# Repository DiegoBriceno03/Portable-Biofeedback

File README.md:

# Portable Biofeedback Device Repository

A repository that stores hardware and software files developed for the Portable Biofeedback Device, as worked on and built by students in the Electrical & Computer Engineering (ECE) Department of the College of Engineering & Computer Science (CECS) at the University of Central Florida (UCF) in Orlando, Florida.

The accompanying Android app was developed in Android Studio 3.5.3, making use of Android SDK/API 21 (Android 5).

All the schematics and layout is done in Kicad 5.14 along with custom libraries. These libraries are added under /Libraries.

These projects use custom path for its libraries. The custom Kicad Path variable ${KI_SDREPO} is used to increase portability. Custom variable points to the physical location of the /Libraries directory and must be declared under "Preferences > Configure Paths" setting before use.

## Group 11 Members

Roles are listed under each group member

+ Grace Brazil (EE)
  + Power circuit design
+ Diego Briceno (EE)
  + PCB design
+ Gustavo Diaz Galeas (CpE)
  + Phone app development
+ Nicholas Miller (CpE)
  + Firmware development

## Hardware

### Breakout Boards
- [x] MAX30101 Heart Rate / Pulse Oximeter Breakout Board REV -
- [x] Galvanic Skin Response Sensor (Groove Seed GSR Sensor design used: https://www.seeedstudio.com/Grove-GSR-sensor-p-1614.html.html)
- [x] Temperature Sensor Supporting Hardware
- [x] Battery Charging Managing circuit (BMS)
- [x] Power Regulation
Integration of these hardware is seen under ~/Prototyp_REV- 

## Software
### Phone App
- [x] Bluetooth backend
- [X] UI / UX

### Firmware
- [x] Heart Rate Data Processing Algorithm
- [x] Temperature Data Processing Algorithm
- [x] Galvanic Skin Resistance Data Processing Algorithm

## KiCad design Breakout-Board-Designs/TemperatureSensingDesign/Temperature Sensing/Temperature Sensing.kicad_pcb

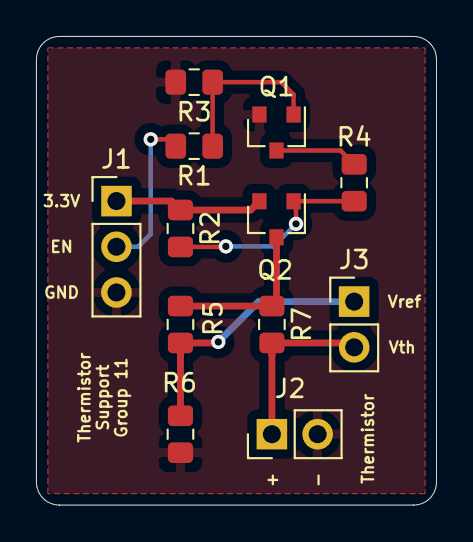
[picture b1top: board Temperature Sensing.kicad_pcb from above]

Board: 2 copper layers, 22.2 x 26.0 mm, 12 parts (0 on the bottom side), 9 nets.

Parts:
J1: POW / Control; PinHeader_1x03_P2.54mm_Vertical
J2: Termistor 10k; PinHeader_1x02_P2.54mm_Vertical
J3: ADC Inputs; PinHeader_1x02_P2.54mm_Vertical
Q1: 2N7002E; SOT-23
Q2: BSS83P; SOT-23
R1, R2, R3, R4, R6: 10k; R_0805_2012Metric_Pad1.15x1.40mm_HandSolder
R5, R7: 20k; R_0805_2012Metric_Pad1.15x1.40mm_HandSolder

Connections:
/+3.3V: J1.1, Q2.2, R2.1
/GPIO_EN: J1.2, R1.2
/Vref: J3.1, R5.2, R6.1
/Vth: J2.1, J3.2, R7.2
GND: J1.3, J2.2, Q1.2, R3.2, R6.2
unnamed: Q1.1, R1.1, R3.1
unnamed: Q1.3, R4.2
unnamed: Q2.1, R2.2, R4.1
unnamed: Q2.3, R5.1, R7.1

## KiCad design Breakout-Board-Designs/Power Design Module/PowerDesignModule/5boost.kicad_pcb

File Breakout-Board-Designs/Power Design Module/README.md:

# Power Design Module.

This module contains the design for the Portable biofeedback anxiety treatment device. 
It consist of a charging circuit (BQ24072) which is configured to charge a single cell LiPo(PKCELL 503035) 500mAh battery. This design takes advantage of a Micro USB charging at CV of 4.2V and CC of 500mA.

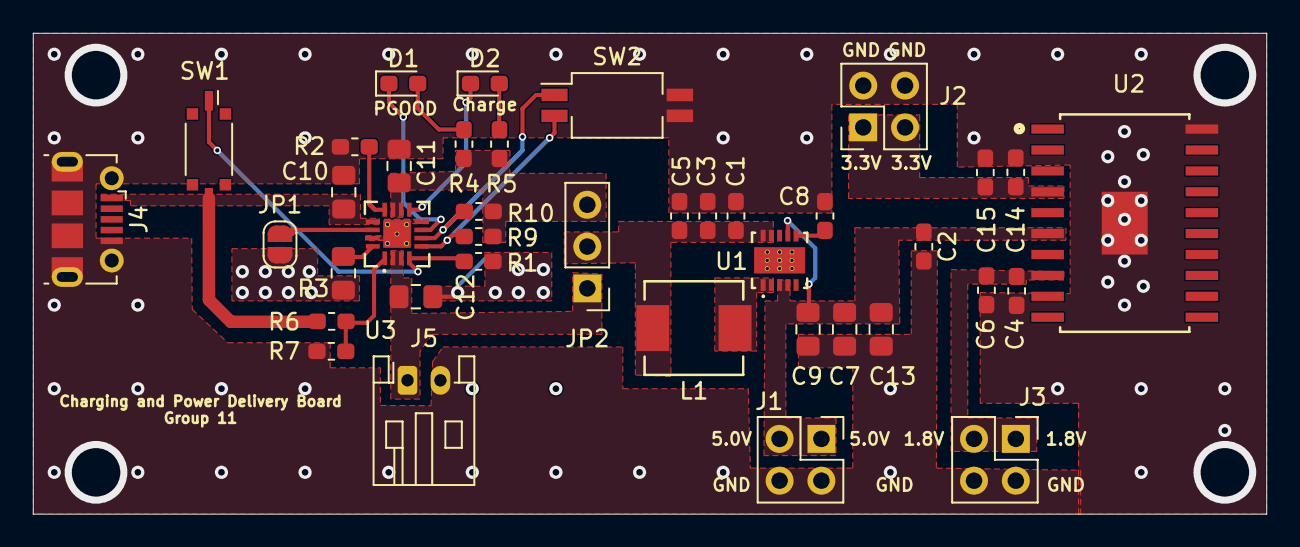
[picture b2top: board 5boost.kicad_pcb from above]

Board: 2 copper layers, 74.9 x 29.2 mm, 39 parts (0 on the bottom side), 21 nets.

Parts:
C1, C3, C5: 10μF; C_0603_1608Metric_Pad1.05x0.95mm_HandSolder
C2, C4, C14: 0.1uF; C_0603_1608Metric_Pad1.05x0.95mm_HandSolder
C6, C15: 10uF; C_0603_1608Metric_Pad1.05x0.95mm_HandSolder
C7, C9, C13: 10uF; C_0805_2012Metric_Pad1.15x1.40mm_HandSolder
C8: 22nF; C_0603_1608Metric_Pad1.05x0.95mm_HandSolder
C10: 1uF; C_0805_2012Metric_Pad1.15x1.40mm_HandSolder
C11, C12: 4.7uF; C_0805_2012Metric_Pad1.15x1.40mm_HandSolder
D1: Red; LED_0603_1608Metric_Pad1.05x0.95mm_HandSolder
D2: Green; LED_0603_1608Metric_Pad1.05x0.95mm_HandSolder
J1: 5.0V; PinSocket_2x02_P2.54mm_Vertical
J2: 3.3V; PinSocket_2x02_P2.54mm_Vertical
J3: 1.8V; PinSocket_2x02_P2.54mm_Vertical
J4: USB_B_Micro; USB_Micro-B_Molex-105017-0001
J5: Battery Output; JST_PH_S2B-PH-K_1x02_P2.00mm_Horizontal
JP1: TMR OFF; SolderJumper-2_P1.3mm_Open_RoundedPad1.0x1.5mm
JP2: Charger / Battery Bypass; PinHeader_1x03_P2.54mm_Vertical
L1: 1uH; IHLP2020BZER1R0M01
R1, R2: 2K; R_0603_1608Metric_Pad1.05x0.95mm_HandSolder
R3: 1.78k; R_0805_2012Metric_Pad1.15x1.40mm_HandSolder
R4: 530R; R_0603_1608Metric_Pad1.05x0.95mm_HandSolder
R5: 320R; R_0603_1608Metric_Pad1.05x0.95mm_HandSolder
R6: 200k; R_0603_1608Metric_Pad1.05x0.95mm_HandSolder
R7: 49.9k; R_0603_1608Metric_Pad1.05x0.95mm_HandSolder
R9, R10: 10k; R_0603_1608Metric_Pad1.05x0.95mm_HandSolder
SW1: Charge Disable Switch; SW_DIP_SPSTx01_Slide_Copal_CVS-01xB_W5.9mm_P1mm
SW2: Input Current Selection; SW_DIP_SPSTx02_Slide_Copal_CHS-02B_W7.62mm_P1.27mm
U1: DRC_S-PVSON-N10; TPS61232DRCR
U2: TPPM0110DWPR
U3: BQ24072TRGTR

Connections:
/1.8V: C4.1, C6.1, J3.1, J3.2, U2.8
/3.3V: C14.1, C15.1, J2.1, J2.2, U2.4
/5.0V: C2.1, C7.1, C9.1, C13.1, J1.1, J1.2, U1.3, U1.4, U1.7, U2.6
/ChargingCircuit/BATT+: C12.1, J5.1, JP2.1, U3.2, U3.3
/Voutbat: C1.2, C3.2, C5.2, JP2.2, L1.1, U1.9, U1.10
EN1: R10.2, SW2.1, U3.6
EN2: R9.1, SW2.2, U3.5
GND: C1.1, C2.2, C3.1, C4.2, C5.1, C6.2, C7.2, C8.2, C9.2, C10.2, C11.2, C12.2, C13.2, C14.2, C15.2, J1.3, J1.4, J2.3, J2.4, J3.3, J3.4, J4.5, J4.6, J5.2, JP1.2, R1.2, R2.2, R3.2, R7.2, SW2.3, SW2.4, U1.11, U2.20, U2.21, U3.8, U3.15, U3.17
unnamed: C8.1, U1.6
unnamed: D1.1, U3.7
unnamed: D1.2, R4.2
unnamed: D2.1, U3.9
unnamed: D2.2, R5.2
unnamed: JP1.1, U3.14
unnamed: L1.2, U1.1, U1.2
unnamed: R2.1, U3.12
unnamed: R3.1, U3.16
unnamed: R6.2, R7.1, U3.1
Vbus: C10.1, J4.1, R6.1, SW1.2, U3.13
Vout: C11.1, JP2.3, R4.1, R5.1, R9.2, R10.1, U3.10, U3.11
~CE: R1.1, SW1.1, U3.4

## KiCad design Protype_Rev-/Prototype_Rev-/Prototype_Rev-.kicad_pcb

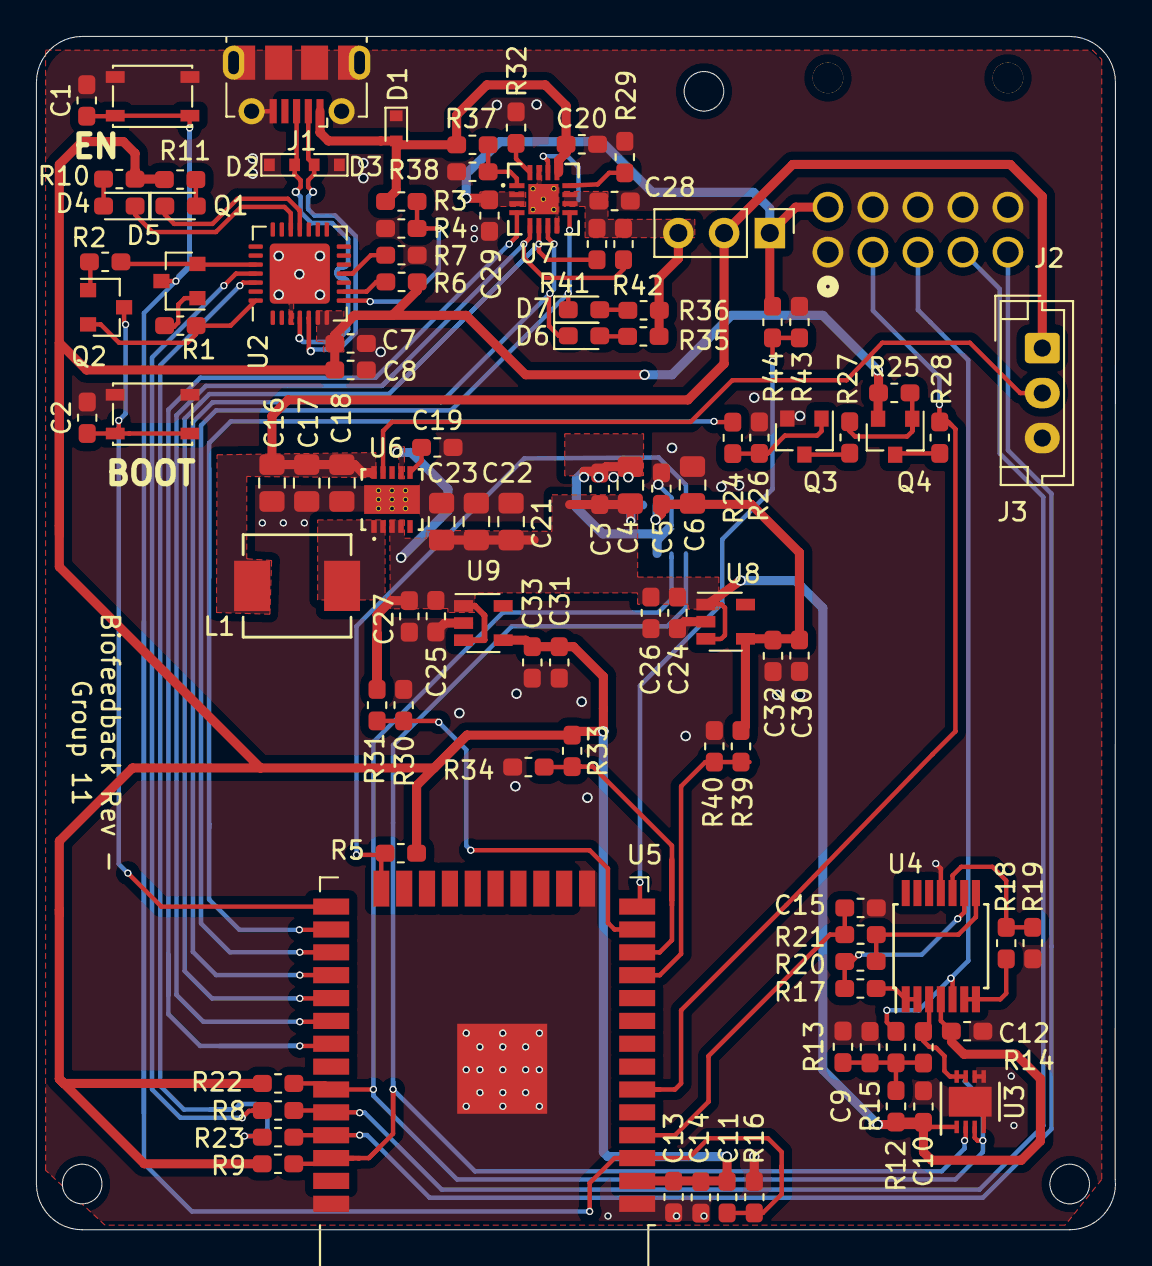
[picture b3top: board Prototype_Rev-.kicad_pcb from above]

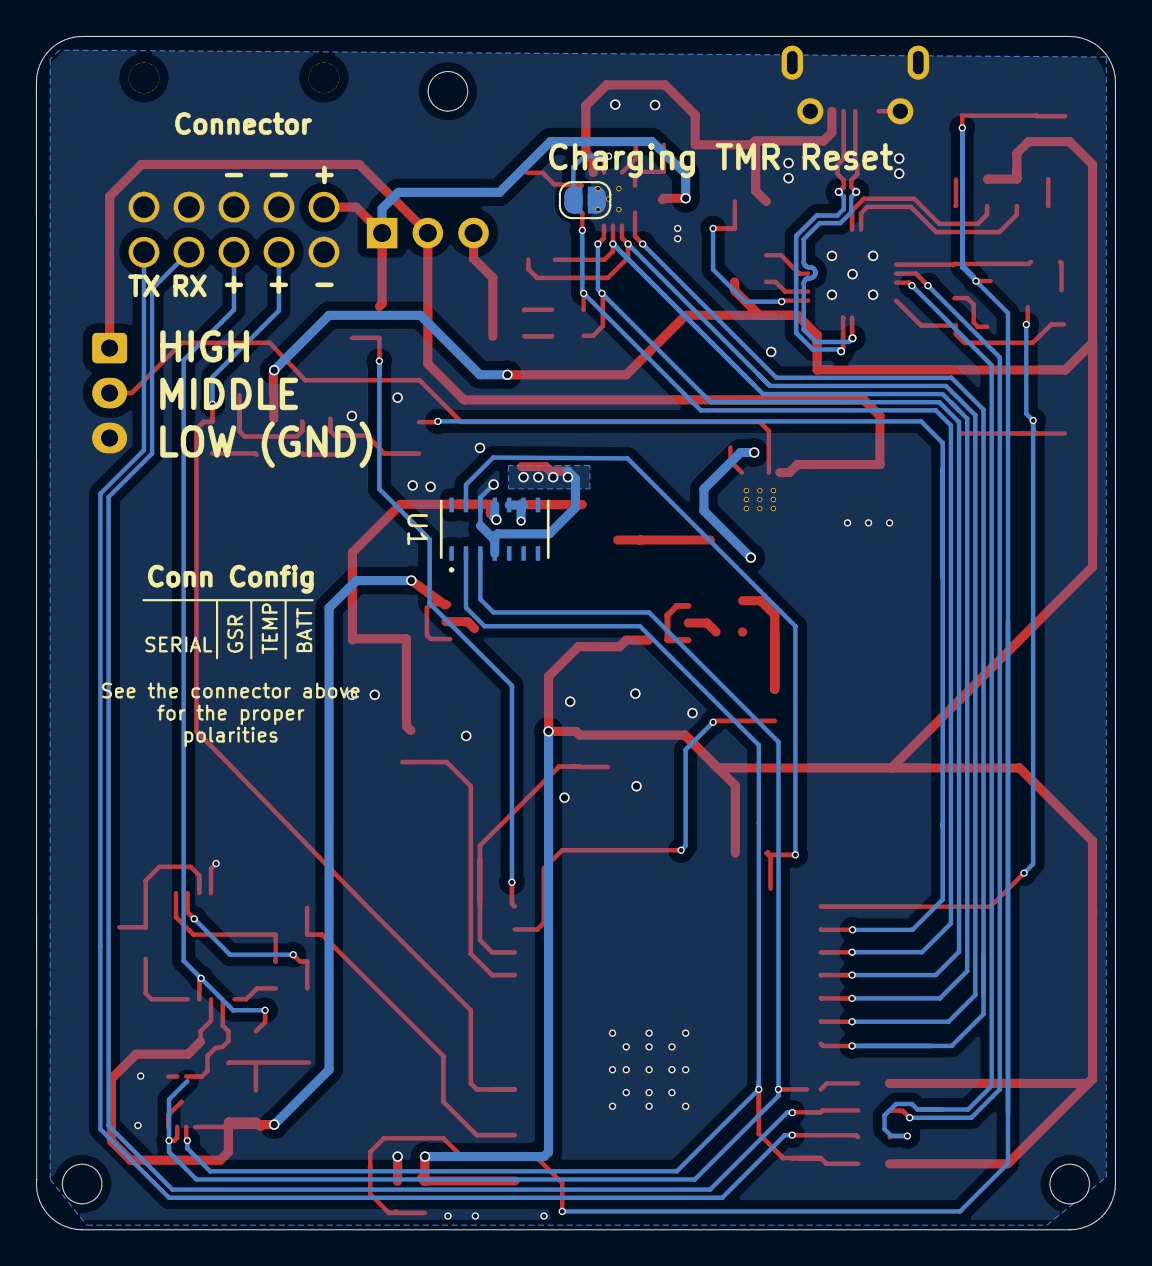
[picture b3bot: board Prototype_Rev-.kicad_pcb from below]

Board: 2 copper layers, 59.9 x 66.3 mm, 106 parts (3 on the bottom side), 64 nets.

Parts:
C1, C2, C7, C10, C11, C12, C13: 0.1uF; C_0603_1608Metric_Pad1.05x0.95mm_HandSolder
C3, C5, C20, C24, C25, C26, C27, C30, C31, C32, C33: 1uF; C_0603_1608Metric_Pad1.05x0.95mm_HandSolder
C4, C6, C16, C17, C18, C21, C22, C23: 10uF; C_0805_2012Metric_Pad1.15x1.40mm_HandSolder
C8, C9, C28, C29: 4.7uF; C_0603_1608Metric_Pad1.05x0.95mm_HandSolder
C14: 22uF; C_0603_1608Metric_Pad1.05x0.95mm_HandSolder
C15: 100nF; C_0603_1608Metric_Pad1.05x0.95mm_HandSolder
C19: 22nF; C_0603_1608Metric_Pad1.05x0.95mm_HandSolder
D1, D2, D3: DESD5V0S1BB-7; D_SOD-523
D4, D5, D6: Red; LED_0603_1608Metric_Pad1.05x0.95mm_HandSolder
D7: Green; LED_0603_1608Metric_Pad1.05x0.95mm_HandSolder
J1: USB_B_Micro; USB_Micro-B_Molex-105017-0001
J2: Interface Hub; 1053141110
J3: Conn_01x02; JST_EH_B3B-EH-A_1x03_P2.50mm_Vertical
JP1: TMR OFF; SolderJumper-2_P1.3mm_Open_RoundedPad1.0x1.5mm
JP2: Charger / Battery Bypass; PinHeader_1x03_P2.54mm_Vertical
L1: 1uH; IHLP2020BZER1R0M01
NT1: AGND - GND; NetTie-2_SMD_Pad0.5mm
Q1, Q2: SS8050-G; SOT-23
Q3: 2N7002ET7G; SOT-23
Q4: BSS83P; SOT-23
R1, R2, R7, R16, R24, R25, R26, R27, R28, R41, R42: 10k; R_0603_1608Metric_Pad1.05x0.95mm_HandSolder
R3: 22.1k; R_0603_1608Metric_Pad1.05x0.95mm_HandSolder
R4: 47.5k; R_0603_1608Metric_Pad1.05x0.95mm_HandSolder
R5, R22, R23: 1.5k; R_0603_1608Metric_Pad1.05x0.95mm_HandSolder
R6, R29: 2K; R_0603_1608Metric_Pad1.05x0.95mm_HandSolder
R8, R9: 0R; R_0603_1608Metric_Pad1.05x0.95mm_HandSolder
R10, R11, R35: 530R; R_0603_1608Metric_Pad1.05x0.95mm_HandSolder
R12, R13: 4.7k; R_0603_1608Metric_Pad1.05x0.95mm_HandSolder
R14, R15, R19, R20, R37: 200k; R_0603_1608Metric_Pad1.05x0.95mm_HandSolder
R17, R18, R30, R31, R33, R34, R39, R40, R43, R44: 100k; R_0603_1608Metric_Pad1.05x0.95mm_HandSolder
R21: 1M; R_0603_1608Metric_Pad1.05x0.95mm_HandSolder
R32: 1.78k; R_0603_1608Metric_Pad1.05x0.95mm_HandSolder
R36: 320R; R_0603_1608Metric_Pad1.05x0.95mm_HandSolder
R38: 49.9k; R_0603_1608Metric_Pad1.05x0.95mm_HandSolder
SW1: EN; SW_SPST_PTS810
SW2: BOOT; SW_SPST_PTS810
U1: MAX30101EFD+
U2: CP2102N-A01-GQFN28; QFN-28-1EP_5x5mm_P0.5mm_EP3.35x3.35mm
U3: MAX5419LETA+; DFN-8-1EP_3x3mm_P0.5mm_EP1.66x2.38mm
U4: LM324; TSSOP-14_4.4x5mm_P0.65mm
U5: ESP32-WROOM-32
U6: TPS61232DRCR
U7: BQ24072TRGTR
U8: TLV75718PDBVR; SOT-23-5
U9: TLV75733PDBVR; SOT-23-5

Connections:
+1V8: C5.1, C6.1, C30.1, C32.1, R39.1, U1.11, U8.4
+3V3: C7.1, C8.1, C13.1, C14.1, C31.1, C33.1, Q4.2, R5.1, R6.1, R10.1, R11.1, R16.1, R22.1, R23.1, R25.1, R33.1, U2.6, U2.7, U5.2, U9.4
+5V: C3.1, C4.1, C10.1, C12.1, C21.1, C22.1, C23.1, C24.1, C25.1, C26.1, C27.1, R12.1, R30.1, U1.9, U1.10, U3.1, U4.4, U6.3, U6.4, U6.7, U8.1, U8.3, U9.1, U9.3
/1.8V_MON: R39.2, R40.1, U5.11
/3.3V_MON: R33.2, R34.1, U5.12
/5V_MON: R30.2, R31.1, U5.13
/BATT+: C29.1, J2.6, JP2.1, R43.1, U7.2, U7.3
/BATT+_MON: R43.2, R44.1, U5.14
/CHRG_EN1: R42.2, U5.29, U7.6
/CHRG_EN2: R41.1, U5.30, U7.5
/EN: C1.1, C11.1, Q1.3, R16.2, SW1.1, U5.3
/GSR+: J2.3, R15.2, U4.5
/GSR_MON: C15.1, R21.2, U5.4
/IO0: C2.1, Q2.3, SW2.1, U5.25
/ON_OFF: J3.2, U6.9
/RXD: R8.1, U2.25
/RXD0: J2.4, R8.2, U5.34
/SCL: R23.2, U1.2, U3.2, U5.36
/SDA: R22.2, U1.3, U3.3, U5.33
/TEMP_EN: R24.2, U5.26
/TXD: R9.2, U2.26
/TXD0: J2.5, R9.1, U5.35
/USB_N: D3.2, J1.2, U2.5
/USB_P: D2.2, J1.3, U2.4
/VOUTBATT: C16.2, C17.2, C18.2, J3.1, JP2.2, L1.1, U6.10
/VTemp: J2.2, R28.2, U5.6
/Vbus: C20.1, D1.2, J1.1, R3.1, R37.1, U7.13
/~BATT_POWGOOD: D6.1, U5.28, U7.7
/~CE: U5.31, U7.4
/~CHRG: D7.1, U5.27, U7.9
/~DTR: Q2.2, R1.1, U2.28
/~INT: R5.2, U1.13, U5.24
/~RTS: Q1.2, R2.1, U2.24
GND: C1.2, C2.2, C5.2, C6.2, C7.2, C8.2, C9.2, C10.2, C11.2, C12.2, C13.2, C14.2, C15.2, C16.1, C17.1, C18.1, C19.1, C20.2, C21.2, C22.2, C23.2, C24.2, C25.2, C26.2, C27.2, C28.2, C29.2, C30.2, C31.2, C32.2, C33.2, D1.1, D2.1, D3.1, J1.5, J1.6, J2.1, J2.7, J2.8, J2.9, J2.10, J3.3, JP1.2, NT1.2, Q3.2, R4.2, R7.2, R13.2, R19.1, R26.2, R29.2, R31.2, R32.2, R34.2, R38.2, R40.2, R44.2, SW1.2, SW2.2, U1.12, U2.3, U2.29, U3.4, U3.5, U3.6, U3.9, U4.11, U5.1, U5.15, U5.38, U5.39, U6.11, U7.8, U7.15, U7.17, U8.2, U9.2
GNDA: C3.2, C4.2, NT1.1, U1.4
unnamed: C9.1, R12.2, R13.1, R14.1, R15.1
unnamed: C19.2, U6.6
unnamed: D4.1, U2.19
unnamed: D4.2, R10.2
unnamed: D5.1, U2.18
unnamed: D5.2, R11.2
unnamed: D6.2, R35.2
unnamed: D7.2, R36.2
unnamed: JP1.1, U7.14
unnamed: L1.2, U6.1, U6.2
unnamed: Q1.1, R1.2
unnamed: Q2.1, R2.2
unnamed: Q3.1, R24.1, R26.1
unnamed: Q3.3, R27.2
unnamed: Q4.1, R25.2, R27.1
unnamed: Q4.3, R28.1
unnamed: R3.2, R4.1, U2.8
unnamed: R6.2, U2.9
unnamed: R7.1, U2.11
unnamed: R14.2, U3.7, U3.8, U4.3
unnamed: R17.1, U4.1, U4.2
unnamed: R17.2, R20.1, U4.9
unnamed: R18.1, U4.6, U4.7
unnamed: R18.2, R19.2, U4.10
unnamed: R20.2, R21.1, U4.8
unnamed: R29.1, U7.12
unnamed: R32.1, U7.16
unnamed: R37.2, R38.1, U7.1
Vout: C28.1, JP2.3, R35.1, R36.1, R41.2, R42.1, U7.10, U7.11

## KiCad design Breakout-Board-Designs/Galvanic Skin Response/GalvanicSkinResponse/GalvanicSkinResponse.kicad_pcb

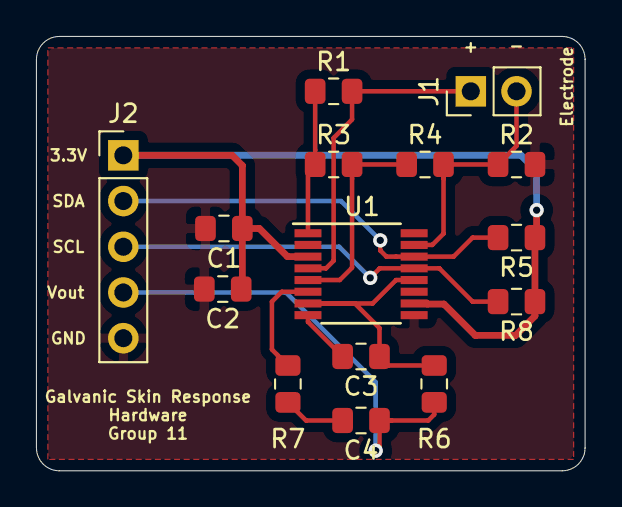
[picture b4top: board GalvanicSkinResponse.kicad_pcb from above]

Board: 2 copper layers, 30.5 x 24.1 mm, 15 parts (0 on the bottom side), 13 nets.

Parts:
C1: 1nF; C_0805_2012Metric_Pad1.15x1.40mm_HandSolder
C2, C4: 10nF; C_0805_2012Metric_Pad1.15x1.40mm_HandSolder
C3: 150pF; C_0805_2012Metric_Pad1.15x1.40mm_HandSolder
J1: Electrodes; PinHeader_1x02_P2.54mm_Vertical
J2: Control; PinHeader_1x05_P2.54mm_Vertical
R1, R6, R7: 100R; R_0805_2012Metric_Pad1.15x1.40mm_HandSolder
R2: 50R; R_0805_2012Metric_Pad1.15x1.40mm_HandSolder
R3: 100k; R_0805_2012Metric_Pad1.15x1.40mm_HandSolder
R4, R5, R8: 15k; R_0805_2012Metric_Pad1.15x1.40mm_HandSolder
U1: PGA309; TSSOP-16_4.4x5mm_P0.65mm

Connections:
+3V3: C1.1, C2.1, J2.1, R5.1, R8.1, U1.3, U1.10
GND: C1.2, C2.2, J2.5, R2.2, U1.2, U1.9, U1.11
unnamed: C3.1, R6.2, U1.7, U1.12
unnamed: C3.2, U1.8
unnamed: C4.2, R7.1
unnamed: J1.1, R1.2, U1.4
unnamed: J1.2, R2.1, R4.2, U1.15
unnamed: R1.1, R3.1, U1.1
unnamed: R3.2, R4.1, U1.5
unnamed: R7.2, U1.6
SCL: J2.3, R8.2, U1.13
SDA: J2.2, R5.2, U1.14
V_out: C4.1, J2.4, R6.1

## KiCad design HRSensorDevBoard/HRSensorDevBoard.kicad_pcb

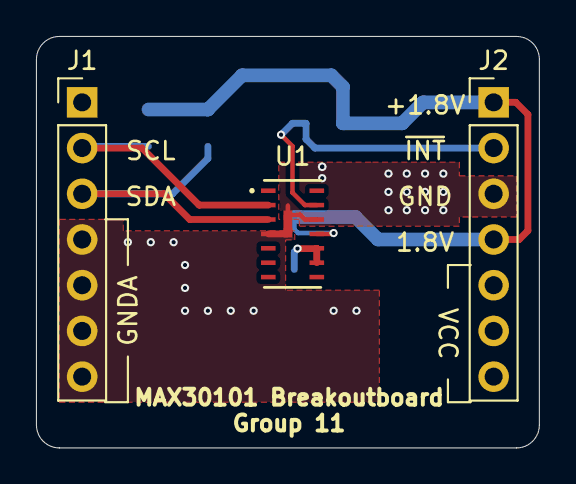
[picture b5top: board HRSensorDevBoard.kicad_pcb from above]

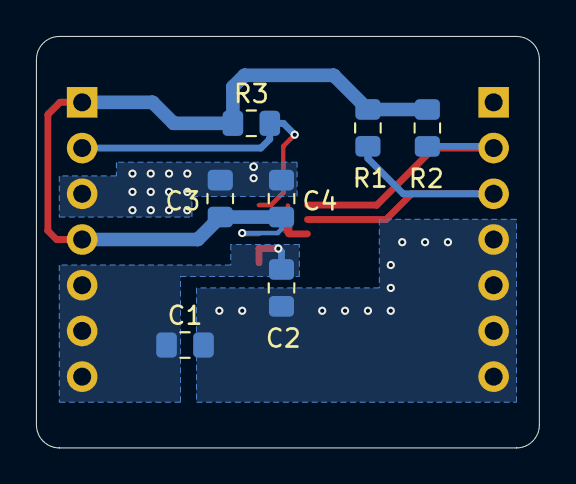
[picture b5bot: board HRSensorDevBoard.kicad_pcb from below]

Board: 2 copper layers, 27.9 x 22.9 mm, 11 parts (7 on the bottom side), 7 nets.

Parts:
C1, C3: 10uF; C_0805_2012Metric_Pad1.15x1.40mm_HandSolder
C2, C4: 1uF; C_0805_2012Metric_Pad1.15x1.40mm_HandSolder
J1: Left; PinHeader_1x07_P2.54mm_Vertical
J2: Right; PinHeader_1x07_P2.54mm_Vertical
NT1: AGND - GND; NetTie-2_SMD_Pad0.5mm
R1, R2, R3: 1.5k; R_0805_2012Metric_Pad1.15x1.40mm_HandSolder
U1: MAX30101EFD+

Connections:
+1V8: C3.1, C4.1, J2.1, J2.4, R1.1, R2.1, R3.1, U1.11
GND: C3.2, C4.2, J2.3, NT1.2, U1.12
GNDA: C1.2, C2.2, J1.4, J1.5, J1.6, J1.7, NT1.1, U1.4
unnamed: J1.2, R2.2, U1.2
unnamed: J1.3, R1.2, U1.3
unnamed: J2.2, R3.2, U1.13
VCC: C1.1, C2.1, J2.5, J2.6, J2.7, U1.9, U1.10

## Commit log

2019-11-11 MAX30101 Breakout board REV- with gerbers
2019-11-11 Added remote repo to Github DiegoBriceno03/Portable-Biofeedback
2019-11-11 Housekeeping
2019-11-11 Added README.md
2019-11-11 Added README.md & modified the .gitignore to go along the new name change
2019-11-24 Separated Breakout Board Design
2019-11-24 Fixed Pictures
2019-11-24 Fixing Images:
2019-11-24 Fixing Formating
2020-01-16 Included new content to the README.md file.
2020-01-16 Small change to README.md file.
2020-01-16 Fixes to README.md file.
2020-01-20 Power board added with temporal design and deleted charging circuit.
2020-01-21 Layout and charging circuit progress.
2020-01-21 Charging circuit and rough layout
2020-01-21 Changes to .gitignore file
2020-01-21 Fine tuning .gitignore file
2020-01-21 Solving merge conflict
2020-01-22 Changes to README.md file; inclusion of /phoneapp directory to store files related to the phone app.
2020-01-22 Finalized Charge board
2020-01-23 Changes done to main README.md file. One was also created for the /phoneapp directory.
2020-01-23 Resolved conflicts in README.md file.
2020-01-25 Reorganized directory hierarchy.
2020-01-25 Included the WiP companion Android app.
2020-01-26 Implementation of basic BLE scan/search and connectivity features.
2020-01-28 Starting Power board Layout. Design Changes
2020-02-06 Final Power Breakout completed. Headers were used instead of the previous Molex Connectors
2020-03-03 Final Power module and App Front end.
2020-03-16 3/16/2020
2020-03-16 Prototype rev - completed. Connectors added and STEP file generated. Phone app progress
2020-03-16 Major overhaul of phone app due to inclusion of custom API that makes BLE development much quicker.
2020-03-18 fixed descriptors
2020-03-18 Latest UX/UI changes.
2020-03-18 New iteration of the phone app.
2020-03-27 Newest revision of phone app.
2020-03-27 Cleaned up file hierarchy. Inclusion of newest version of phone app.
2020-04-08 Implemented additional code into MainActivity. Got working navigation bar functionality. Set-up notify alerts to user.
2020-04-10 Simplistic implementation of intended purpose of NotificationsActivity.
2020-04-10 QoL improvements across DashboardActivity, NotificationsActivity, and Utils.
2020-04-11 Final revision of the phone app. Made small change to GSR text value in DashboardActivity.
2020-04-13 Changes to hierarchy.
2020-04-13 Renamed directory.
2020-05-01 Changes done to main README.
